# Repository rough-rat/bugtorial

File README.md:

# bugtorial

This badge was made for a workshop. The main topic for the event was "upcycling" - therefore we designed the badge around reusability of old components - the legs and antennas are made from scrap electronic components (we have a lot of these at hackerspace), so are resistors and LEDs too (who uses THT components today anyways).

## License

This repository contains two separately licensed things:

### Hardware — CERN-OHL-P v2

Copyright © 2026 Jakub "critbit" Sadowski.

The electronic design (schematics, PCB layout, routing, and the other design
files in this repository, excluding the artwork described below) is Open
Hardware, licensed under the CERN Open Hardware Licence Version 2 - Permissive.
You may redistribute and modify it under the terms of the
[CERN-OHL-P v2](LICENSES/CERN-OHL-P-2.0.txt) (https://ohwr.org/cern_ohl_p_v2.txt).

It is distributed WITHOUT ANY EXPRESS OR IMPLIED WARRANTY, INCLUDING OF
MERCHANTABILITY, SATISFACTORY QUALITY AND FITNESS FOR A PARTICULAR PURPOSE.
Please see the CERN-OHL-P v2 for applicable conditions.

### Artwork — CC BY-NC-SA 4.0

Copyright © 2026 @weasel.

The artwork is licensed separately from the hardware. The drawings in the
`.svg` files, and the same graphics where they appear in the PCB and
fabrication files (silkscreen, copper, solder mask and board outline, including
Gerbers and other manufacturing outputs), are licensed under
[Creative Commons Attribution-NonCommercial-ShareAlike 4.0 International](LICENSES/CC-BY-NC-SA-4.0.txt)
(https://creativecommons.org/licenses/by-nc-sa/4.0/).

Because the artwork is part of the board layout, a badge manufactured from
these files as-is includes it, so the non-commercial and share-alike conditions
apply to such badges. The CERN-OHL-P terms apply on their own only to the design
with the artwork removed or replaced.

### Other licensing

If the licenses above don't fit what you have in mind, for example running
workshops or events with these badges, or making them in larger batches,
get in touch. We're open to licensing this work on different terms.

Visit [roughrat.com](https://roughrat.com) for contact info.

### How to credit

When you share or build on this project, please credit it like this:

> bugtorial: hardware by Jakub "critbit" Sadowski (CERN-OHL-P v2),
> artwork by @weasel (CC BY-NC-SA 4.0).

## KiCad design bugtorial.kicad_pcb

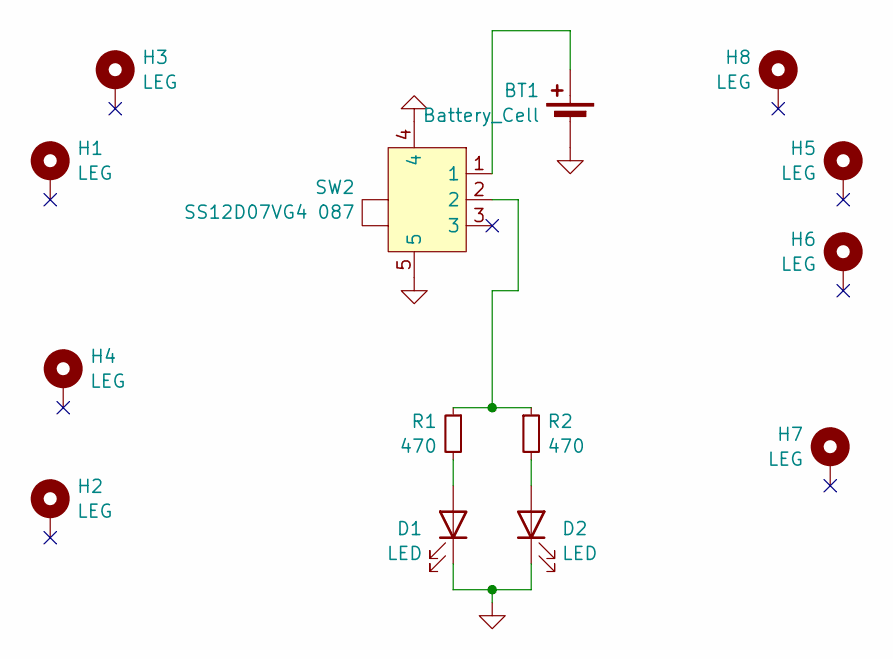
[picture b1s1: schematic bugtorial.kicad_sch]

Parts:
BT1: Battery_Cell; BatteryHolder_Keystone_1060_1x2032
D1, D2: LED; LED_D1.8mm_W1.8mm_H2.4mm_Horizontal_O1.27mm_Z1.6mm
H1, H2, H3, H4, H5, H6, H7, H8: LEG; TestPoint_THTPad_D2.0mm_Drill1.0mm
R1, R2: 470; R_Axial_DIN0207_L6.3mm_D2.5mm_P10.16mm_Horizontal
SW2: SS12D07VG4 087; SW-TH_SS12D07VG4; MPN SS12D07VG4 087; LCSC Part C2939726

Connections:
GND: BT1.2 (-), D1.1 (K), D2.1 (K), SW2.4, SW2.5
unnamed: BT1.1 (+), SW2.1
unnamed: D1.2 (A), R1.2
unnamed: D2.2 (A), R2.2
unnamed: R1.1, R2.1, SW2.2

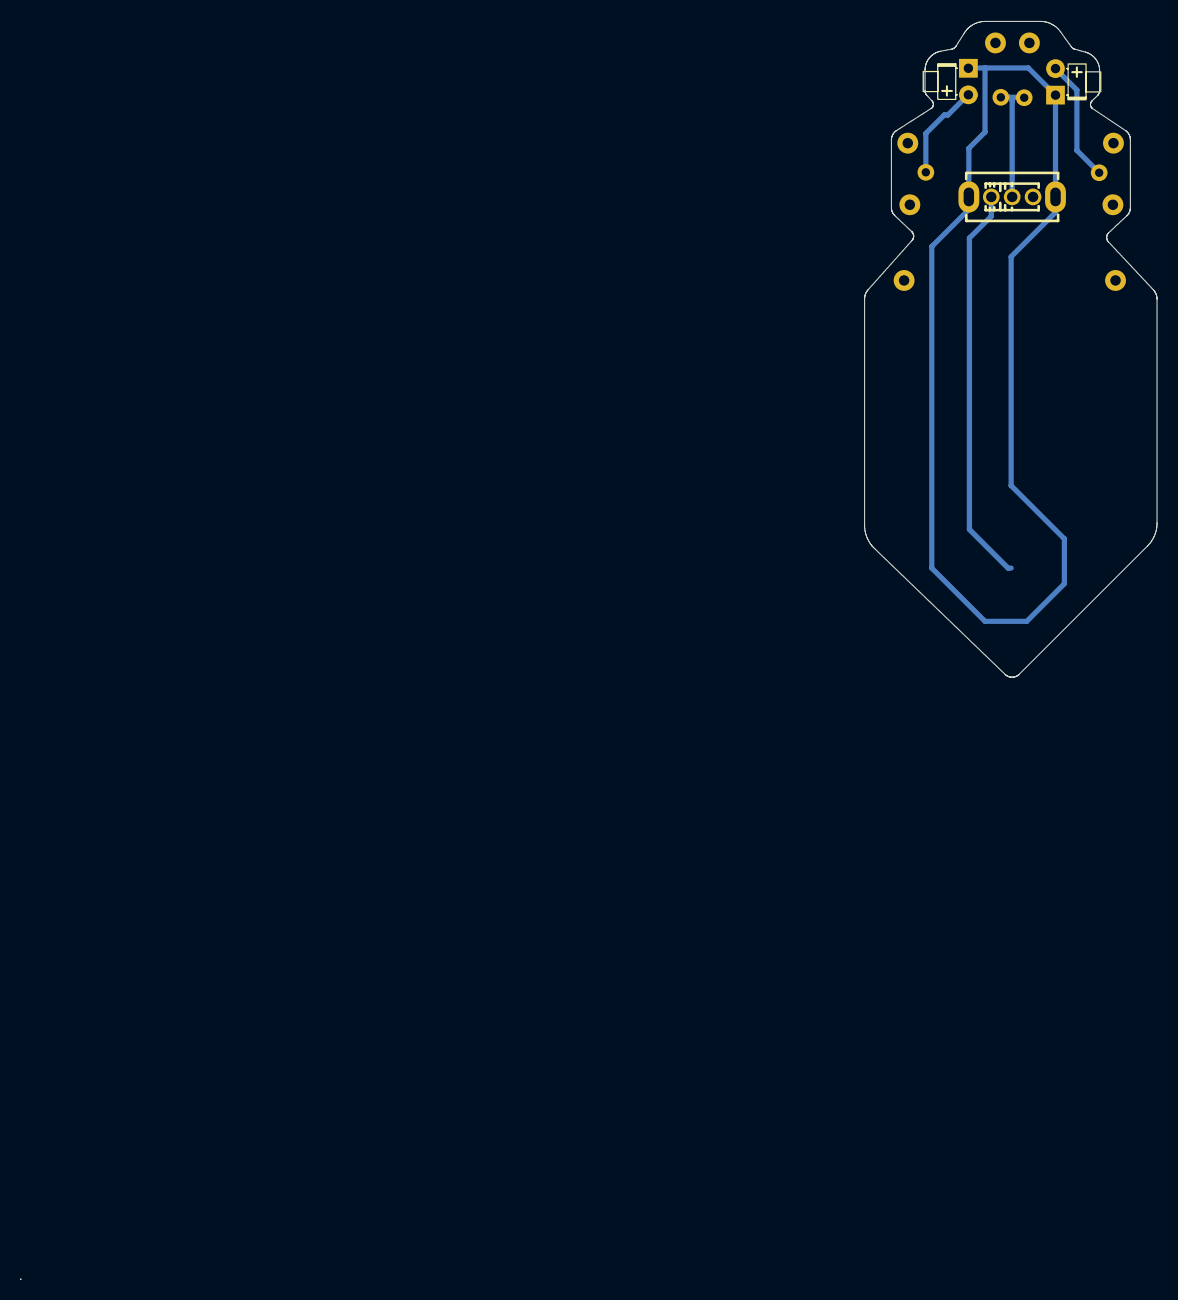
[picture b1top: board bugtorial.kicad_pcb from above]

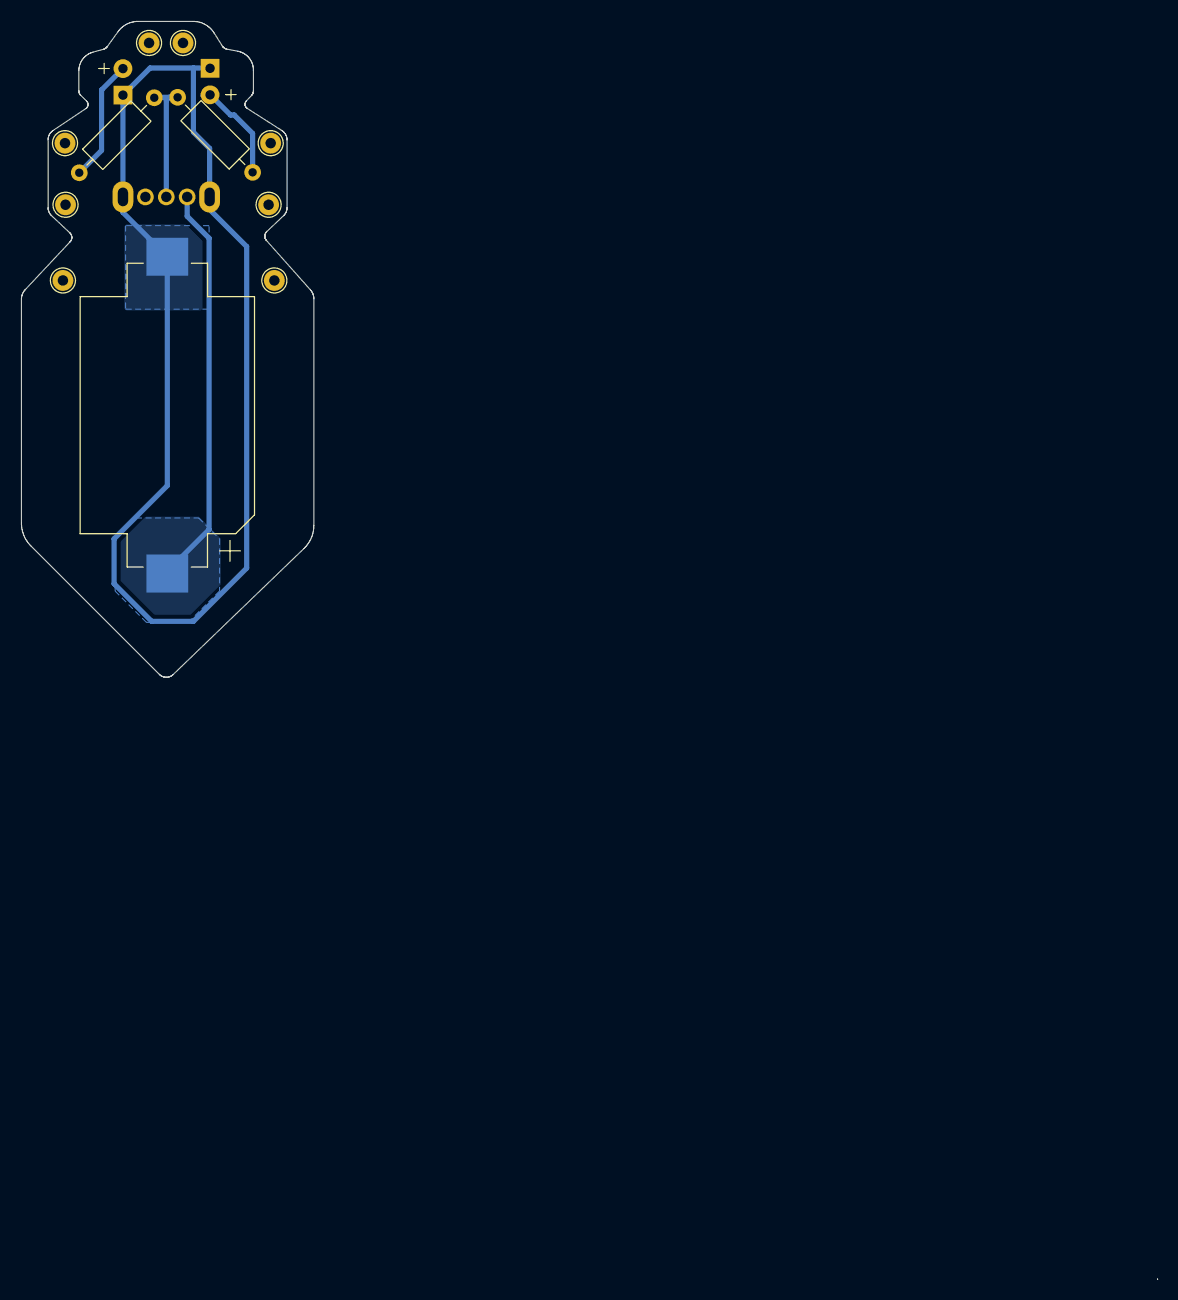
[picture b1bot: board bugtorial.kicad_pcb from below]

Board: 2 copper layers, 28.0 x 62.8 mm, 14 parts (11 on the bottom side), 5 nets.

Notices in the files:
bugtorial.kicad_pcb:
SPDX-License-Identifier: CERN-OHL-P-2.0 AND CC-BY-NC-SA-4.0
SPDX-FileCopyrightText: 2026 Jakub \"critbit\" Sadowski (hardware), @weasel (artwork)
Licenses: see LICENSES/ and README.md
